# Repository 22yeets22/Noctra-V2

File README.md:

<h1 align="center">
  Noctra Devboard
  <br>
</h1>

<h4 align="center">
A RP2350 based devboard with esp c6 mini integration for wifi + bluetooth.
</h4>
<br>

<div align="center">

| Front Render                            | PCB                         |
| --------------------------------------- | --------------------------- |
|  |  |

</div>

<h2>Overview</h2>
- A main MCU (RP2350) for input / output pins
- A coprocessor (ESP32-C6 Mini) for wireless connectivity
- Power management (USB + battery support with battery charging)

<h3>Hardware Specs</h3>
- RP2350 microcontroller
- ESP32-C6 Mini (Wi-Fi + Bluetooth via ESP-AT)
- External 16MB flash memory (128Mbit)
- Power System
  - TPS63100 buck-boost converter: 2A, 1.6V – 5.5V, 3V3_EN pin
  - TPS2116 power mux: Auto-switch between USB and battery (~3V threshold)
  - HX4054A battery charger: 500mA + indicator LED
- USB-C, with TPD2EUSB30 ESD protection for data lines
- ADC filtering + ADC_VREF pin

<h2>How to Use</h2>
Like a normal Pico:
1. Power the board via USB-C, while holding down BOOTSEL to enter firmware writing mode.
2. Flash firmware by dragging in the firmware file.
3. Use onboard GPIO headers as you would with a standard Pico, but with wifi connectivity.

<h3>Motivation</h3>
After making my previous devboard, I wanted something with WiFi + bluetooth, so I came up with this new board. It has everything the previous board has, but better, with better power management, battery charging, and everything I could possibly want.

<h2>Firmware</h2>
Current firmware is untested, but we should be able to use the Challenger+ firmware as the topology and pins are the same. You can find the firmware in the firmware folder.

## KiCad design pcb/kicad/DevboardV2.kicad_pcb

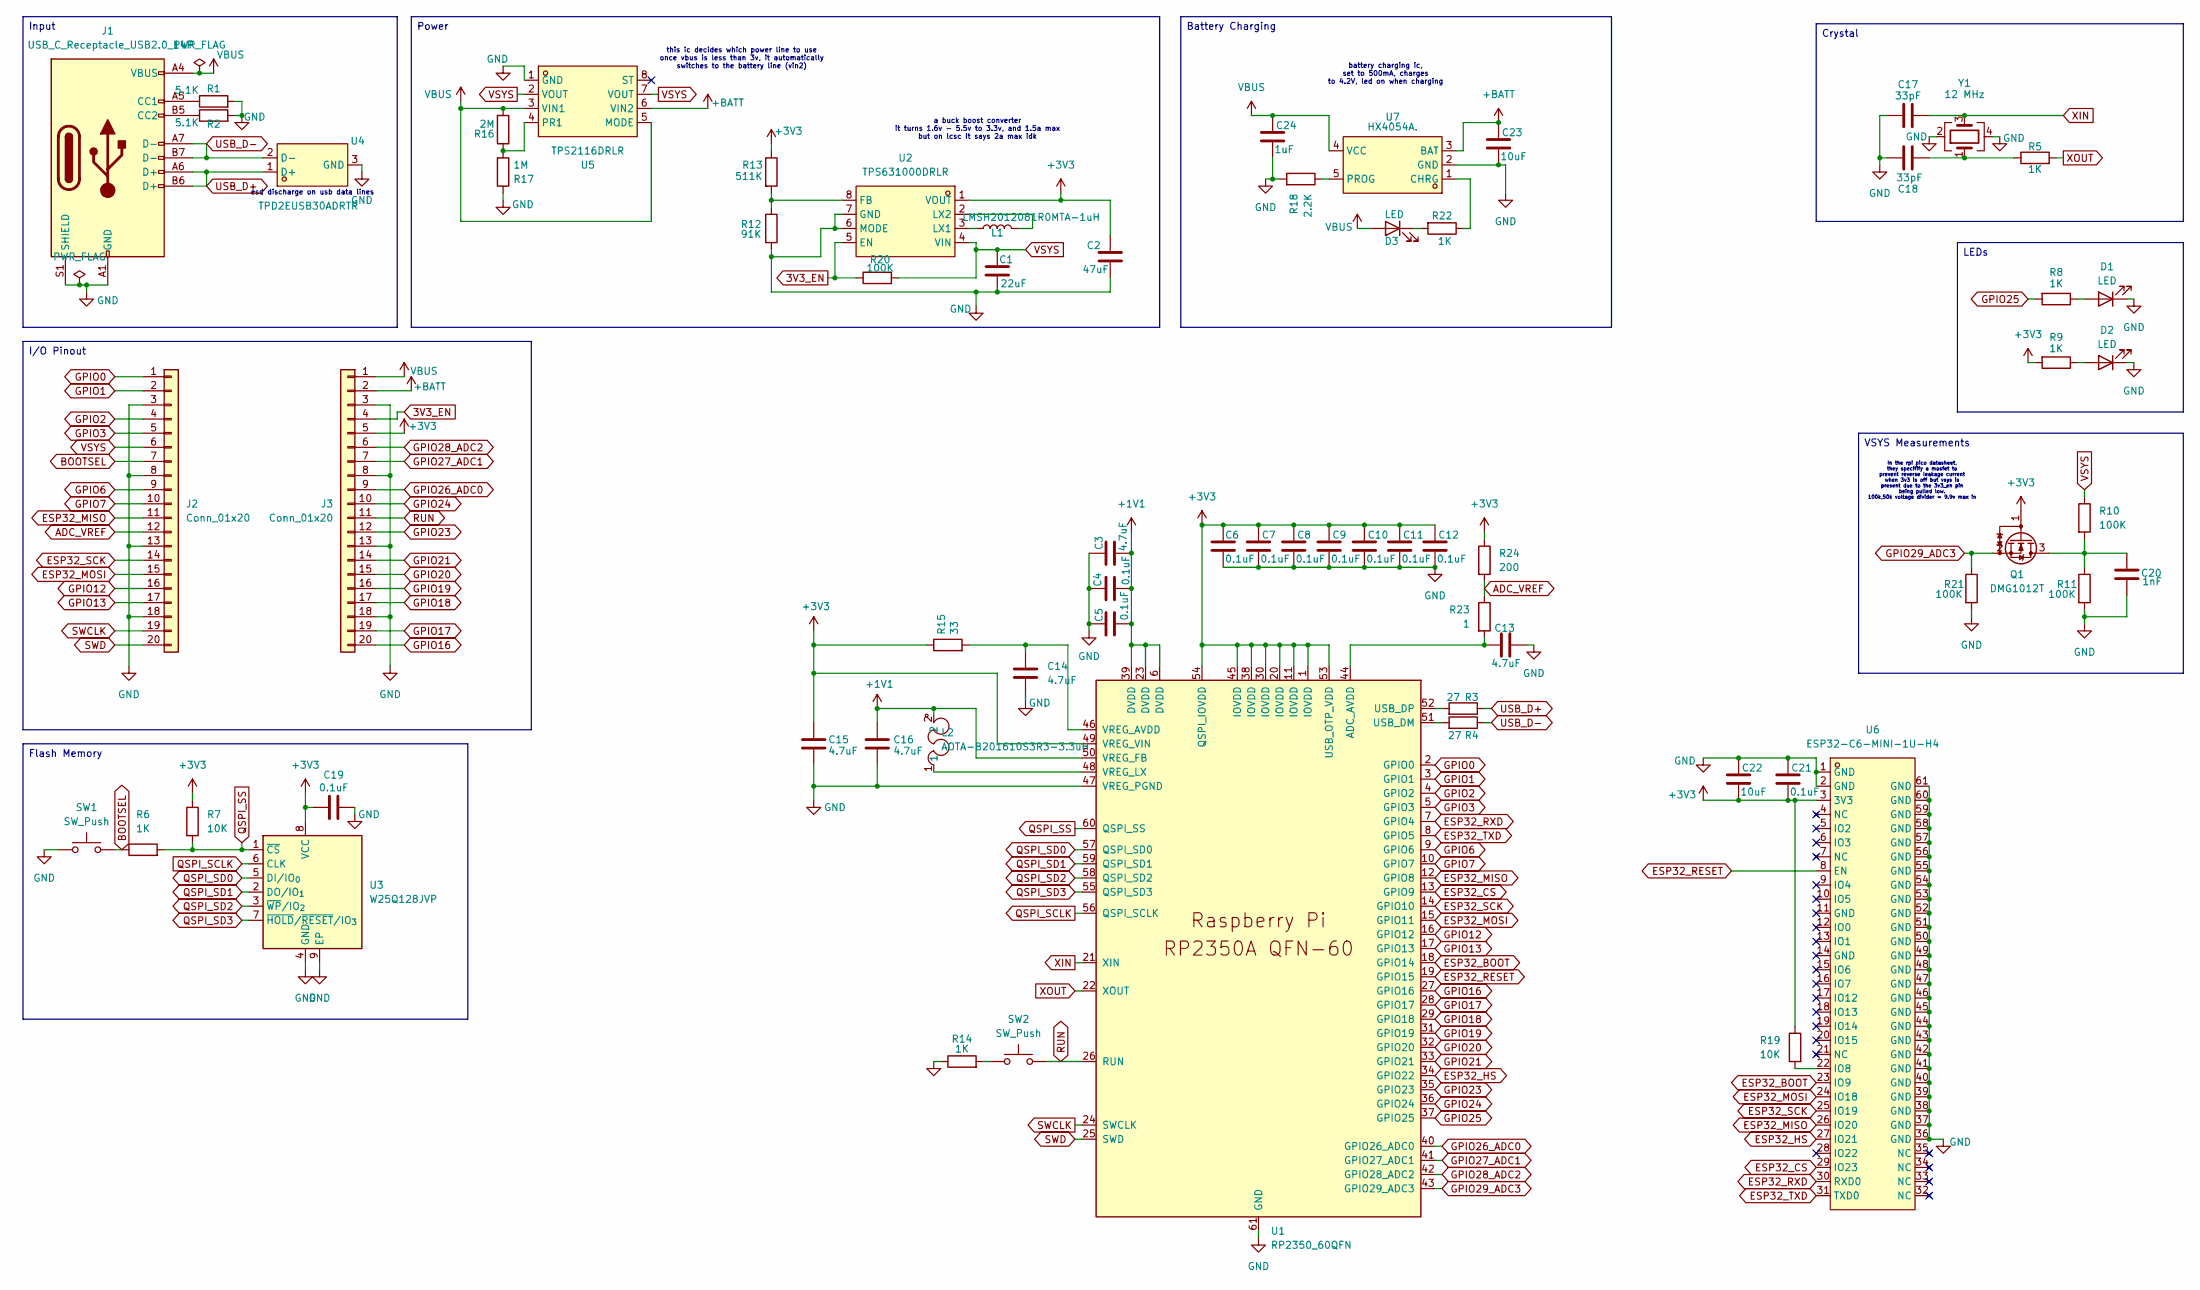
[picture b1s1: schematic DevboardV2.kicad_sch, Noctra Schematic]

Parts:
C1: 22uF; C_0603_1608Metric
C2: 47uF; C_0805_2012Metric
C3, C13, C14, C15, C16: 4.7uF; C_0402_1005Metric
C4, C5, C6, C7, C8, C9, C10, C11, C12, C19, C21: 0.1uF; C_0402_1005Metric
C17, C18: 33pF; C_0402_1005Metric
C20: 1nF; C_0402_1005Metric
C22, C23: 10uF; C_0402_1005Metric
C24: 1uF; C_0402_1005Metric
D1, D2, D3: LED; LED_0402_1005Metric
J1: USB_C_Receptacle_USB2.0_14P; USB_C_Receptacle_HRO_TYPE-C-31-M-12
J2, J3: Conn_01x20; PinHeader_1x20_P2.54mm_Vertical
L1: LMSH2012081R0MTA-1uH; L_0805_2012Metric
L2: AOTA-B201610S3R3-3.3uH; IND-SMD_L2.0-W1.6_AOTA-B201610S3R3-101-T; LCSC Part C42411119
Q1: DMG1012T; SOT-523
R1, R2: 5.1K; R_0402_1005Metric
R3, R4: 27; R_0402_1005Metric
R5, R6, R8, R9, R14, R22: 1K; R_0402_1005Metric
R7, R19: 10K; R_0402_1005Metric
R10, R11, R20, R21: 100K; R_0402_1005Metric
R12: 91K; R_0402_1005Metric
R13: 511K; R_0402_1005Metric
R15: 33; R_0402_1005Metric
R16: 2M; R_0402_1005Metric
R17: 1M; R_0402_1005Metric
R18: 2.2K; R_0402_1005Metric
R23: 1; R_0201_0603Metric
R24: 200; R_0201_0603Metric
SW1, SW2: SW_Push; SW_Push_SPST_NO_Alps_SKRK
U1: RP2350_60QFN; QFN-60-1EP_7x7mm_P0.4mm_EP3.4x3.4mm_ThermalVias
U2: TPS631000DRLR; SOT-583-8_L2.1-W1.2-P0.50-LS1.6-BL; LCSC Part C5219190
U3: W25Q128JVP; WSON-8-1EP_6x5mm_P1.27mm_EP3.4x4.3mm
U4: TPD2EUSB30ADRTR; SOT-723_L1.2-W0.8-P0.80-LS1.2-BR; LCSC Part C5182099
U5: TPS2116DRLR; SOT-583-8_L2.1-W1.6-P0.50-LS1.6-BL; LCSC Part C3235557
U6: ESP32-C6-MINI-1U-H4; WIFIM-SMD_61P-L13.2-W12.5-P0.80; LCSC Part C20627095
U7: HX4054A.; TSOT-23-5_L2.9-W1.6-P0.95-LS2.8-BL; LCSC Part C52952905
Y1: 12 MHz; Crystal_SMD_3225-4Pin_3.2x2.5mm

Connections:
3V3_EN: J3.4, R20.1, U2.5 (EN)
+1V1: C3.2, C4.2, C5.2, C16.1, L2.2, U1.6 (DVDD), U1.23 (DVDD), U1.39 (DVDD), U1.50 (VREG_FB)
+3V3: C2.1, C6.1, C7.1, C8.1, C9.1, C10.1, C11.1, C12.1, C15.1, C19.1, C21.2, C22.2, J3.5, Q1.1 (G), R7.1, R9.2, R13.1, R15.1, R19.1, R24.1, U1.1 (IOVDD), U1.11 (IOVDD), U1.20 (IOVDD), U1.30 (IOVDD), U1.38 (IOVDD), U1.45 (IOVDD), U1.49 (VREG_VIN), U1.53 (USB_OTP_VDD), U1.54 (QSPI_IOVDD), U2.1 (VOUT), U3.8 (VCC), U6.3 (3V3)
+BATT: C23.1, J3.2, U5.6 (VIN2), U7.3 (BAT)
ADC_VREF: J2.12, R23.1, R24.2
BOOTSEL: J2.7, R6.1, SW1.2
ESP32_BOOT: U1.18 (GPIO14), U6.23 (IO9)
ESP32_CS: U1.13 (GPIO9), U6.29 (IO23)
ESP32_HS: U1.34 (GPIO22), U6.27 (IO21)
ESP32_MISO: J2.11, U1.12 (GPIO8), U6.26 (IO20)
ESP32_MOSI: J2.15, U1.15 (GPIO11), U6.24 (IO18)
ESP32_RESET: U1.19 (GPIO15), U6.8 (EN)
ESP32_RXD: U1.7 (GPIO4), U6.30 (RXD0)
ESP32_SCK: J2.14, U1.14 (GPIO10), U6.25 (IO19)
ESP32_TXD: U1.8 (GPIO5), U6.31 (TXD0)
GND: C1.2, C2.2, C3.1, C4.1, C5.1, C6.2, C7.2, C8.2, C9.2, C10.2, C11.2, C12.2, C13.2, C14.2, C15.2, C16.2, C17.1, C18.1, C19.2, C20.2, C21.1, C22.1, C23.2, C24.2, D1.1 (K), D2.1 (K), J1.A1 (GND), J1.A12 (GND), J1.B1 (GND), J1.B12 (GND), J1.S1 (SHIELD), J2.3, J2.8, J2.13, J2.18, J3.3, J3.8, J3.13, J3.18, R1.2, R2.2, R11.2, R12.2, R14.1, R17.1, R18.2, R21.2, SW1.1, U1.47 (VREG_PGND), U1.61 (GND), U2.6 (MODE), U2.7 (GND), U3.4 (GND), U3.9 (EP), U4.3 (GND), U5.1 (GND), U6.1 (GND), U6.2 (GND), U6.36 (GND), U6.37 (GND), U6.38 (GND), U6.39 (GND), U6.40 (GND), U6.41 (GND), U6.42 (GND), U6.43 (GND), U6.44 (GND), U6.45 (GND), U6.46 (GND), U6.47 (GND), U6.48 (GND), U6.49 (GND), U6.50 (GND), U6.51 (GND), U6.52 (GND), U6.53 (GND), U6.54 (GND), U6.55 (GND), U6.56 (GND), U6.57 (GND), U6.58 (GND), U6.59 (GND), U6.60 (GND), U6.61 (GND), U7.2 (GND), Y1.2, Y1.4
GPIO0: J2.1, U1.2 (GPIO0)
GPIO1: J2.2, U1.3 (GPIO1)
GPIO2: J2.4, U1.4 (GPIO2)
GPIO3: J2.5, U1.5 (GPIO3)
GPIO6: J2.9, U1.9 (GPIO6)
GPIO7: J2.10, U1.10 (GPIO7)
GPIO12: J2.16, U1.16 (GPIO12)
GPIO13: J2.17, U1.17 (GPIO13)
GPIO16: J3.20, U1.27 (GPIO16)
GPIO17: J3.19, U1.28 (GPIO17)
GPIO18: J3.17, U1.29 (GPIO18)
GPIO19: J3.16, U1.31 (GPIO19)
GPIO20: J3.15, U1.32 (GPIO20)
GPIO21: J3.14, U1.33 (GPIO21)
GPIO23: J3.12, U1.35 (GPIO23)
GPIO24: J3.10, U1.36 (GPIO24)
GPIO25: R8.2, U1.37 (GPIO25)
GPIO26_ADC0: J3.9, U1.40 (GPIO26_ADC0)
GPIO27_ADC1: J3.7, U1.41 (GPIO27_ADC1)
GPIO28_ADC2: J3.6, U1.42 (GPIO28_ADC2)
GPIO29_ADC3: Q1.2 (S), R21.1, U1.43 (GPIO29_ADC3)
unnamed: C18.2, R5.1, Y1.1
unnamed: D1.2 (A), R8.1
unnamed: D2.2 (A), R9.1
unnamed: D3.1 (K), R22.2
unnamed: J1.A5 (CC1), R1.1
unnamed: J1.B5 (CC2), R2.1
unnamed: C20.1, Q1.3 (D), R10.2, R11.1
unnamed: R14.2, SW2.2
unnamed: C13.1, R23.2, U1.44 (ADC_AVDD)
unnamed: R4.2, U1.51 (USB_DM)
unnamed: R3.2, U1.52 (USB_DP)
unnamed: C14.1, R15.2, U1.46 (VREG_AVDD)
unnamed: L2.1, U1.48 (VREG_LX)
unnamed: R12.1, R13.2, U2.8 (FB)
unnamed: L1.2, U2.3 (LX1)
unnamed: L1.1, U2.2 (LX2)
unnamed: R16.1, R17.2, U5.4 (PR1)
unnamed: R19.2, U6.22 (IO8)
unnamed: R22.1, U7.1 (CHRG)
unnamed: R18.1, U7.5 (PROG)
QSPI_SCLK: U1.56 (QSPI_SCLK), U3.6 (CLK)
QSPI_SD0: U1.57 (QSPI_SD0), U3.5 (DI/IO_{0})
QSPI_SD1: U1.59 (QSPI_SD1), U3.2 (DO/IO_{1})
QSPI_SD2: U1.58 (QSPI_SD2), U3.3 (~WP/IO_{2})
QSPI_SD3: U1.55 (QSPI_SD3), U3.7 (~HOLD/~RESET/IO_{3})
QSPI_SS: R6.2, R7.2, U1.60 (QSPI_SS), U3.1 (~CS)
RUN: J3.11, SW2.1, U1.26 (RUN)
SWCLK: J2.19, U1.24 (SWCLK)
SWD: J2.20, U1.25 (SWD)
USB_D+: J1.A6 (D+), J1.B6 (D+), R3.1, U4.1 (D+)
USB_D-: J1.A7 (D-), J1.B7 (D-), R4.1, U4.2 (D-)
VBUS: C24.1, D3.2 (A), J1.A4 (VBUS), J1.A9 (VBUS), J1.B4 (VBUS), J1.B9 (VBUS), J3.1, R16.2, U5.3 (VIN1), U5.5 (MODE), U7.4 (VCC)
VSYS: C1.1, J2.6, R10.1, R20.2, U2.4 (VIN), U5.2 (VOUT), U5.7 (VOUT)
XIN: C17.2, U1.21 (XIN), Y1.3
XOUT: R5.2, U1.22 (XOUT)

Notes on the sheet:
this ic decides which power line to use once vbus is less than 3v, it automatically switches to the battery line (vin2)
esd discharge on usb data lines
battery charging ic, set to 500mA, charges to 4.2V, led on when charging
In the rpi pico datasheet, they specifify a mosfet to prevent reverse leakage current when 3v3 is off but vsys is present due to the 3v3_en pin being pulled low. 100k,50k voltage divider = 9.9v max in
a buck boost converter it turns 1.6v - 5.5v to 3.3v, and 1.5a max but on lcsc it says 2a max idk
Power
Input
LEDs
Battery Charging
VSYS Measurements
Flash Memory
I/O Pinout
Crystal

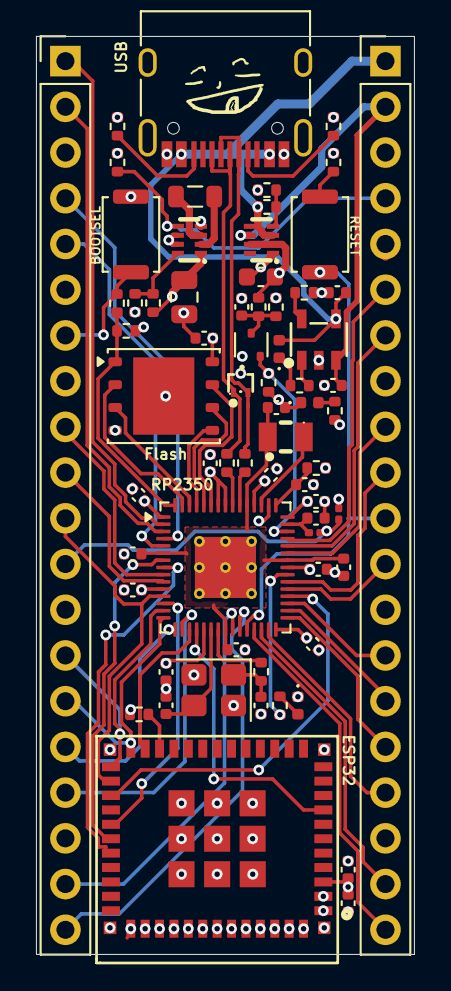
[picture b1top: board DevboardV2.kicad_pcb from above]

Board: 4 copper layers, 21.0 x 51.0 mm, 67 parts (0 on the bottom side), 72 nets.

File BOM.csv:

"Id";"Designator";"Footprint";"Quantity";"Designation";"Supplier and ref";
1;"J1";"USB_C_Receptacle_HRO_TYPE-C-31-M-12";1;"USB_C_Receptacle_USB2.0_14P";;;
2;"C12,C5,C10,C21,C4,C11,C19,C6,C8,C9,C7";"C_0402_1005Metric";11;"0.1uF";;;
3;"R20,R11,R21,R10";"R_0402_1005Metric";4;"100K";;;
4;"L1";"L_0805_2012Metric";1;"LMSH2012081R0MTA-1uH";;;
5;"C15,C13,C3,C14,C16";"C_0402_1005Metric";5;"4.7uF";;;
6;"C1";"C_0603_1608Metric";1;"22uF";;;
7;"C2";"C_0805_2012Metric";1;"47uF";;;
8;"R9,R6,R5,R14,R8,R22";"R_0402_1005Metric";6;"1K";;;
9;"Y1";"Crystal_SMD_3225-4Pin_3.2x2.5mm";1;"12 MHz";;;
10;"R18";"R_0402_1005Metric";1;"2.2K";;;
11;"R19,R7";"R_0402_1005Metric";2;"10K";;;
12;"C24";"C_0402_1005Metric";1;"1uF";;;
13;"R3,R4";"R_0402_1005Metric";2;"27";;;
14;"D3,D1,D2";"LED_0402_1005Metric";3;"LED";;;
15;"U6";"WIFIM-SMD_61P-L13.2-W12.5-P0.80";1;"ESP32-C6-MINI-1U-H4";;;
16;"C20";"C_0402_1005Metric";1;"1nF";;;
17;"U4";"SOT-723_L1.2-W0.8-P0.80-LS1.2-BR";1;"TPD2EUSB30ADRTR";;;
18;"Q1";"SOT-523";1;"DMG1012T";;;
19;"C23,C22";"C_0402_1005Metric";2;"10uF";;;
20;"C17,C18";"C_0402_1005Metric";2;"33pF";;;
21;"L2";"IND-SMD_L2.0-W1.6_AOTA-B201610S3R3-101-T";1;"AOTA-B201610S3R3-3.3uH";;;
22;"U5";"SOT-583-8_L2.1-W1.6-P0.50-LS1.6-BL";1;"TPS2116DRLR";;;
23;"SW2,SW1";"SW_Push_SPST_NO_Alps_SKRK";2;"SW_Push";;;
24;"J3,J2";"PinHeader_1x20_P2.54mm_Vertical";2;"Conn_01x20";;;
25;"R13";"R_0402_1005Metric";1;"511K";;;
26;"R12";"R_0402_1005Metric";1;"91K";;;
27;"R15";"R_0402_1005Metric";1;"33";;;
28;"R17";"R_0402_1005Metric";1;"1M";;;
29;"R24";"R_0201_0603Metric";1;"200";;;
30;"U7";"TSOT-23-5_L2.9-W1.6-P0.95-LS2.8-BL";1;"HX4054A.";;;
31;"R1,R2";"R_0402_1005Metric";2;"5.1K";;;
32;"U2";"SOT-583-8_L2.1-W1.2-P0.50-LS1.6-BL";1;"TPS631000DRLR";;;
33;"R23";"R_0201_0603Metric";1;"1";;;
34;"U1";"QFN-60-1EP_7x7mm_P0.4mm_EP3.4x3.4mm_ThermalVias";1;"RP2350_60QFN";;;
35;"R16";"R_0402_1005Metric";1;"2M";;;
36;"U3";"WSON-8-1EP_6x5mm_P1.27mm_EP3.4x4.3mm";1;"W25Q128JVP";;;

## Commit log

2026-04-03 Revise README with project details and usage instructions
    Updated README to include detailed project information, hardware specs, usage instructions, and motivation for development.
2026-04-03 readme, bom, gerbers, p&p, images
